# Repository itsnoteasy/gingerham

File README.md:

# Decided to name it Donegal, after the tweed.

a fork of the gingham keyboard pcb which adds abnt2 to iso_uk and ansi 60% layout but drops the i/o expander and vias.

made with kicad 5 nightly development build. Upgrade if it will not open.

https://github.com/yiancar/gingham_pcb

there is a backlit version here https://github.com/itsnoteasy/misc/blob/master/donegal_abnt2.zip

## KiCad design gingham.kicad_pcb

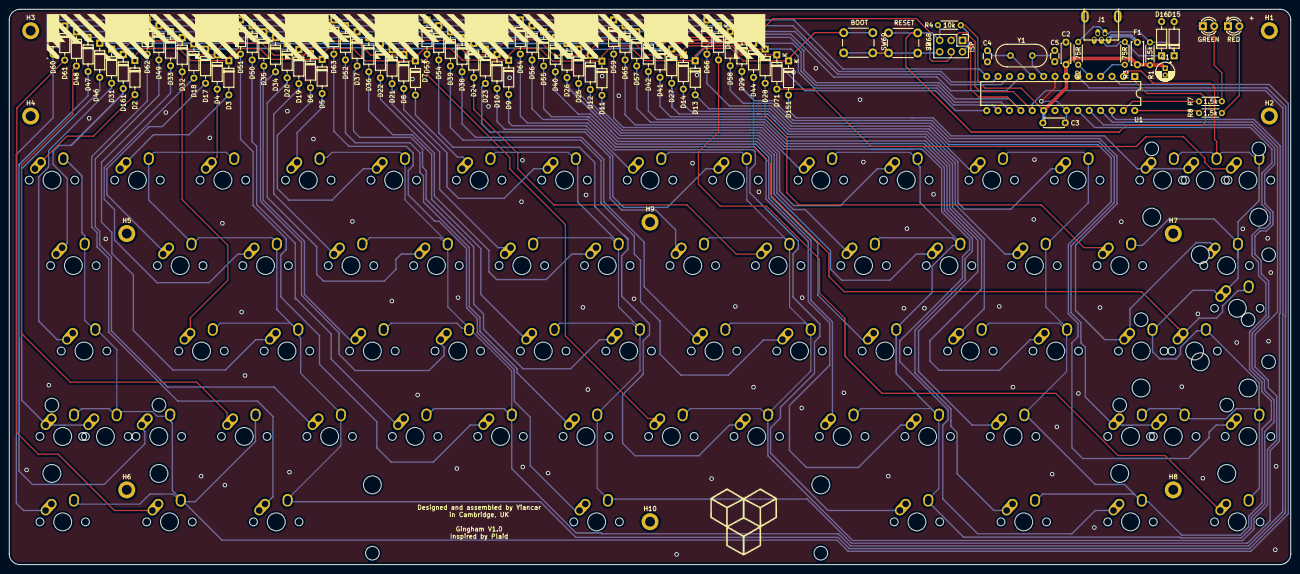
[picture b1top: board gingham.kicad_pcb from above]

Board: 2 copper layers, 285.8 x 123.8 mm, 166 parts (0 on the bottom side), 94 nets.

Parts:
C1: 4.7u; CP_Radial_D4.0mm_P1.50mm
C2, C3: 100n; C_Disc_D4.3mm_W1.9mm_P5.00mm
C4, C5: 22p; C_Disc_D3.0mm_W1.6mm_P2.50mm
D2, D3, D4, D5, D6, D7, D8, D9, D10, D11, D12, D13, D14, D17, D18, D19, D20, D21, D22, D23, D24, D25, D26, D27, D28, D29, D31, D32, D33, D34, D35, D36, D37, D38, D39, D40, D41, D42, D44, D46, D47, D48, D49, D50, D51, D52, D53, D54, D55, D56, D57, D58, D59, D60, D61, D62, D63, D64, D65, D66, D67, D71, D151, D161: 1N4148; D_DO-35_SOD27_P7.62mm_Horizontal
D15, D16: 3.6V; D_DO-35_SOD27_P7.62mm_Horizontal
F1: 100mA; C_Disc_D5.0mm_W2.5mm_P5.00mm
H1, H2, H3, H4, H5, H6, H7, H8, H9, H10: M2; MountingHole_2.2mm_M2_DIN965_Pad
J1: Molex-0548190519
J2: ISP; PinHeader_2x03_P2.54mm_Vertical
LED1: RED; LED_D3.0mm_Clear
LED2: GREEN; LED_D3.0mm_Clear
R1, R7, R8: 1.5k; R_Axial_DIN0204_L3.6mm_D1.6mm_P5.08mm_Horizontal
R2, R3: 75R; R_Axial_DIN0204_L3.6mm_D1.6mm_P5.08mm_Horizontal
R4: 10k; R_Axial_DIN0204_L3.6mm_D1.6mm_P5.08mm_Horizontal
SW1: SW_Push; MX-2U-NoLED
SW2, SW3, SW4, SW5, SW6, SW7, SW8, SW9, SW10, SW11, SW12, SW13, SW14, SW15, SW17, SW18, SW19, SW20, SW21, SW22, SW23, SW24, SW25, SW26, SW27, SW28, SW29, SW32, SW33, SW34, SW35, SW36, SW37, SW38, SW39, SW40, SW41, SW42, SW47, SW48, SW49, SW50, SW51, SW52, SW53, SW54, SW55, SW56, SW57, SW59, SW71: SW_Push; MX-1U-NoLED
SW16, SW43: SW_Push; MX-1.5U-NoLED
SW30: SW_Push; MX-ISO-ReversedStabilizers
SW31, SW45: SW_Push; MX-1.75U-NoLED
SW44, SW46: SW_Push; MX-2.25U-NoLED
SW58: SW_Push; MX-2.75U-NoLED
SW60, SW61, SW62, SW64, SW65, SW66, SW67, SW70: SW_Push; MX-1.25U-NoLED
SW63: SW_Push; MX-6.25U-ReversedStabilizers-NoLED
SW68: RESET; SW_PUSH_6mm
SW69: BOOT; SW_PUSH_6mm
U1: ATMEGA328-PU; DIP-28_W7.62mm
Y1: 16MHz; Crystal_HC49-4H_Vertical
svg2mod: G***; gingham

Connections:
+5V: C1.1, C2.1, C3.1, F1.2, J2.2, R1.2, R4.1, U1.7, U1.20
/COL0: SW2.2, SW16.2, SW31.2, SW46.2, SW47.2, SW48.2, SW60.2, SW61.2, SW70.2, U1.3
/COL1: SW3.2, SW4.2, SW17.2, SW18.2, SW32.2, SW33.2, SW49.2, SW62.2, U1.6
/COL2: J2.3, SW5.2, SW6.2, SW19.2, SW20.2, SW34.2, SW35.2, SW50.2, SW51.2, U1.19
/COL3: SW7.2, SW8.2, SW21.2, SW22.2, SW36.2, SW37.2, SW52.2, SW63.2, U1.26
/COL4: SW9.2, SW10.2, SW23.2, SW24.2, SW38.2, SW39.2, SW53.2, SW54.2, U1.25
/COL5: SW11.2, SW12.2, SW25.2, SW26.2, SW40.2, SW55.2, SW56.2, SW64.2, U1.24
/COL6: SW13.2, SW14.2, SW27.2, SW41.2, SW42.2, SW57.2, SW65.2, SW66.2, U1.23
/COL7: SW1.2, SW15.2, SW28.2, SW29.2, SW30.2, SW43.2, SW44.2, SW45.2, SW58.2, SW59.2, SW67.2, SW71.2, U1.2
/RESET: J2.5, R4.2, SW68.1, U1.1
/ROW0: D2.1, D3.1, D5.1, D7.1, D9.1, D11.1, D13.1, D151.1, SW69.1, U1.11
/ROW1: D4.1, D6.1, D8.1, D10.1, D12.1, D14.1, D71.1, D161.1, U1.15
/ROW2: D17.1, D19.1, D21.1, D23.1, D25.1, D27.1, D28.1, D31.1, U1.16
/ROW3: D18.1, D20.1, D22.1, D24.1, D26.1, D41.1, D44.1, D46.1, J2.4, U1.17
/ROW4: D29.1, D32.1, D34.1, D36.1, D38.1, D40.1, D42.1, D47.1, J2.1, U1.18
/ROW5: D33.1, D35.1, D37.1, D39.1, D48.1, D55.1, D57.1, D58.1, U1.12
/ROW6: D49.1, D50.1, D52.1, D54.1, D56.1, D61.1, D65.1, D67.1, U1.13
/ROW7: D51.1, D53.1, D59.1, D60.1, D62.1, D63.1, D64.1, D66.1, U1.14
/USB_D+: R3.1, U1.4
/USB_D-: R2.1, U1.5
GND: C1.2, C2.2, C3.2, C4.2, C5.2, D15.2, D16.2, J1.1, J1.6, J2.6, LED1.1, LED2.1, SW68.2, SW69.2, U1.8, U1.22
unnamed: C4.1, U1.10, Y1.2
unnamed: C5.1, U1.9, Y1.1
unnamed: D2.2, SW2.1
unnamed: D3.2, SW3.1
unnamed: D4.2, SW4.1
unnamed: D5.2, SW5.1
unnamed: D6.2, SW6.1
unnamed: D7.2, SW7.1
unnamed: D8.2, SW8.1
unnamed: D9.2, SW9.1
unnamed: D10.2, SW10.1
unnamed: D11.2, SW11.1
unnamed: D12.2, SW12.1
unnamed: D13.2, SW13.1
unnamed: D14.2, SW14.1
unnamed: D15.1, J1.4, R1.1, R2.2
unnamed: D16.1, J1.3, R3.2
unnamed: D17.2, SW17.1
unnamed: D18.2, SW18.1
unnamed: D19.2, SW19.1
unnamed: D20.2, SW20.1
unnamed: D21.2, SW21.1
unnamed: D22.2, SW22.1
unnamed: D23.2, SW23.1
unnamed: D24.2, SW24.1
unnamed: D25.2, SW25.1
unnamed: D26.2, SW26.1
unnamed: D27.2, SW27.1
unnamed: D28.2, SW28.1
unnamed: D29.2, SW29.1, SW43.1
unnamed: D31.2, SW31.1
unnamed: D32.2, SW32.1
unnamed: D33.2, SW33.1
unnamed: D34.2, SW34.1
unnamed: D35.2, SW35.1
unnamed: D36.2, SW36.1
unnamed: D37.2, SW37.1
unnamed: D38.2, SW38.1
unnamed: D39.2, SW39.1
unnamed: D40.2, SW40.1
unnamed: D41.2, SW41.1
unnamed: D42.2, SW42.1
unnamed: D44.2, SW30.1, SW44.1
unnamed: D46.2, SW46.1, SW70.1
unnamed: D47.2, SW47.1
unnamed: D48.2, SW48.1
unnamed: D49.2, SW49.1
unnamed: D50.2, SW50.1
unnamed: D51.2, SW51.1
unnamed: D52.2, SW52.1
unnamed: D53.2, SW53.1
unnamed: D54.2, SW54.1
unnamed: D55.2, SW55.1
unnamed: D56.2, SW56.1
unnamed: D57.2, SW57.1
unnamed: D58.2, SW45.1, SW58.1
unnamed: D59.2, SW66.1
unnamed: D60.2, SW60.1
unnamed: D61.2, SW61.1
unnamed: D62.2, SW62.1
unnamed: D63.2, SW63.1
unnamed: D64.2, SW64.1
unnamed: D65.2, SW65.1
unnamed: D66.2, SW59.1
unnamed: D67.2, SW67.1
unnamed: D71.2, SW71.1
unnamed: D151.2, SW1.1, SW15.1
unnamed: D161.2, SW16.1
unnamed: F1.1, J1.5
unnamed: LED1.2, R8.2
unnamed: LED2.2, R7.2
unnamed: R7.1, U1.27
unnamed: R8.1, U1.28
